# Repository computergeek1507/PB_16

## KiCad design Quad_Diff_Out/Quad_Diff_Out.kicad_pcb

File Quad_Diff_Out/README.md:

# Copyright and Disclaimer
Copyright: Scott Hanson

This documentation describes Open Hardware and is licensed under the CERN Open Hardware License Version 2 - Strongly Reciprocal. (CERN-OHL-S)

You may redistribute and modify this documentation under the terms of the CERN OHL-S-v2 (https://ohwr.org/cern_ohl_s_v2.txt). This documentation is distributed WITHOUT ANY EXPRESS OR IMPLIED WARRANTY, INCLUDING OF MERCHANTABILITY, SATISFACTORY QUALITY AND FITNESS FOR A PARTICULAR PURPOSE. Please see the CERN OHL v2-S for applicable conditions

**Under CERN OHL-S-v2, derivative work must be publicly released as defined in subsection 3.3**

# Quad Diff Out

The Quad Diff Out is a single Differental Reciever output board for the PB16. It works with Smart and Dumb Differental Recievers. All the design files are open source and available on github.

## [Part BOM](https://github.com/computergeek1507/PB_16/raw/master/Quad_Diff_Out/Quad_Diff_Out_BOM.ods)

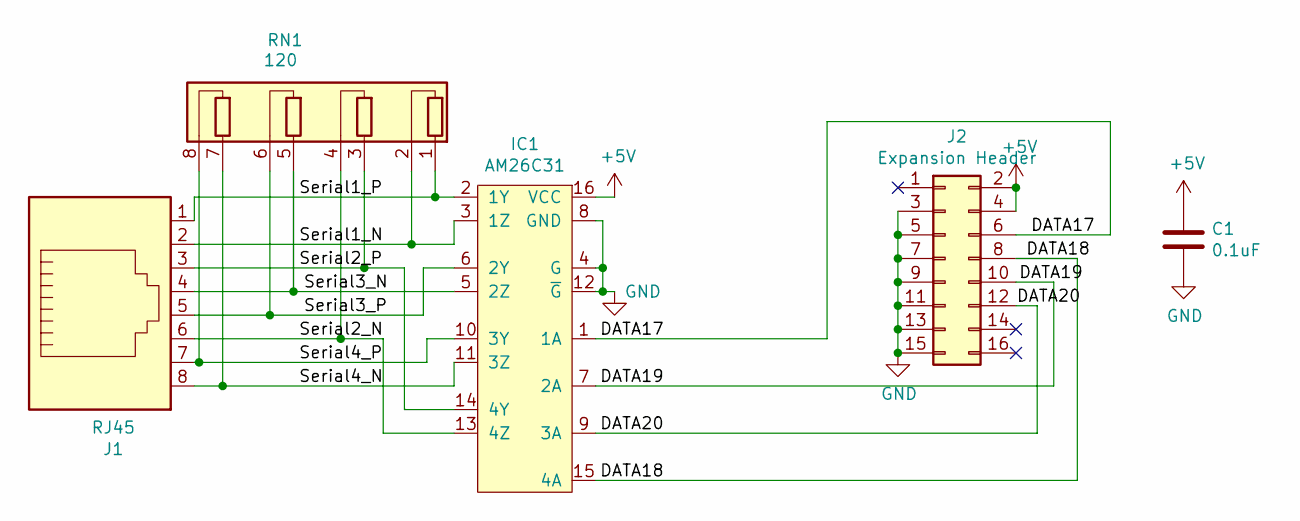
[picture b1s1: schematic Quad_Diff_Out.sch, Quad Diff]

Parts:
C1: 0.1uF; C_Rect_L7.0mm_W2.0mm_P5.00mm; Digikey PN 478-7336-1-ND
IC1: AM26C31; DIP-16_W7.62mm; Farnell 4975637
J1: RJ45; RJ45_Amphenol_54602-x08_Horizontal; Digikey PN AE10392-ND
J2: Expansion Header; PinSocket_2x08_P2.54mm_Vertical; Digikey PN S7111-ND
RN1: 120; R_Array_SIP8; Digikey PN 4608X-2-121LF-ND

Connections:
+5V: C1.1, IC1.16 (VCC), J2.2, J2.4
/DATA17: IC1.1 (1A), J2.6
/DATA18: IC1.15 (4A), J2.8
/DATA19: IC1.7 (2A), J2.10
/DATA20: IC1.9 (3A), J2.12
/Serial1_N: IC1.3 (1Z), J1.2, RN1.2 (R1.2)
/Serial1_P: IC1.2 (1Y), J1.1, RN1.1 (R1.1)
/Serial2_N: IC1.13 (4Z), J1.6, RN1.4 (R2.2)
/Serial2_P: IC1.14 (4Y), J1.3, RN1.3 (R2.1)
/Serial3_N: IC1.5 (2Z), J1.4, RN1.5 (R3.1)
/Serial3_P: IC1.6 (2Y), J1.5, RN1.6 (R3.2)
/Serial4_N: IC1.11 (3Z), J1.8, RN1.7 (R4.1)
/Serial4_P: IC1.10 (3Y), J1.7, RN1.8 (R4.2)
GND: C1.2, IC1.4 (G), IC1.8 (GND), IC1.12 (~G), J2.3, J2.5, J2.7, J2.9, J2.11, J2.13, J2.15

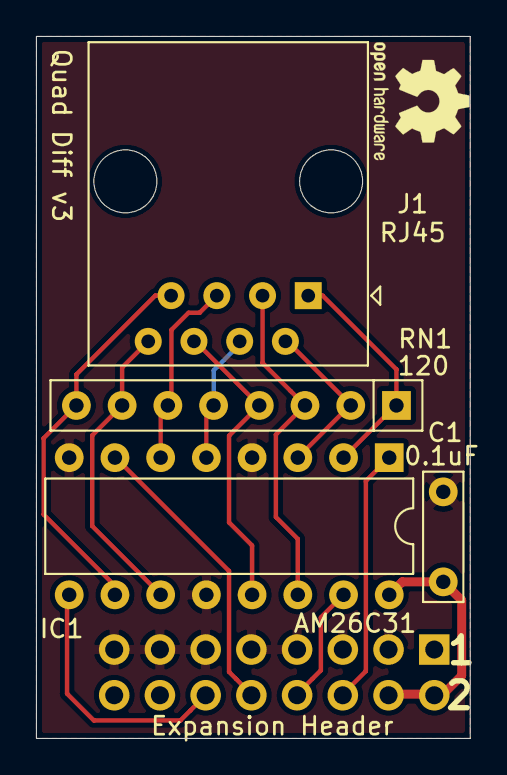
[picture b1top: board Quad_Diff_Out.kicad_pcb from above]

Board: 2 copper layers, 24.1 x 39.0 mm, 5 parts (1 on the bottom side), 14 nets.

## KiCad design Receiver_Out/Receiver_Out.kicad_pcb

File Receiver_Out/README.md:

# Copyright and Disclaimer
Copyright: Scott Hanson

This documentation describes Open Hardware and is licensed under the CERN Open Hardware License Version 2 - Strongly Reciprocal. (CERN-OHL-S)

You may redistribute and modify this documentation under the terms of the CERN OHL-S-v2 (https://ohwr.org/cern_ohl_s_v2.txt). This documentation is distributed WITHOUT ANY EXPRESS OR IMPLIED WARRANTY, INCLUDING OF MERCHANTABILITY, SATISFACTORY QUALITY AND FITNESS FOR A PARTICULAR PURPOSE. Please see the CERN OHL v2-S for applicable conditions

**Under CERN OHL-S-v2, derivative work must be publicly released as defined in subsection 3.3**

# Receiver Out

The "Receiver Out" is a 4 port Differental Reciver output board for the PB16.  All the design files are open source and available on github.

## [Part BOM](https://github.com/computergeek1507/PB_16/raw/master/Receiver_Out/Receiver_Out_BOM.ods)

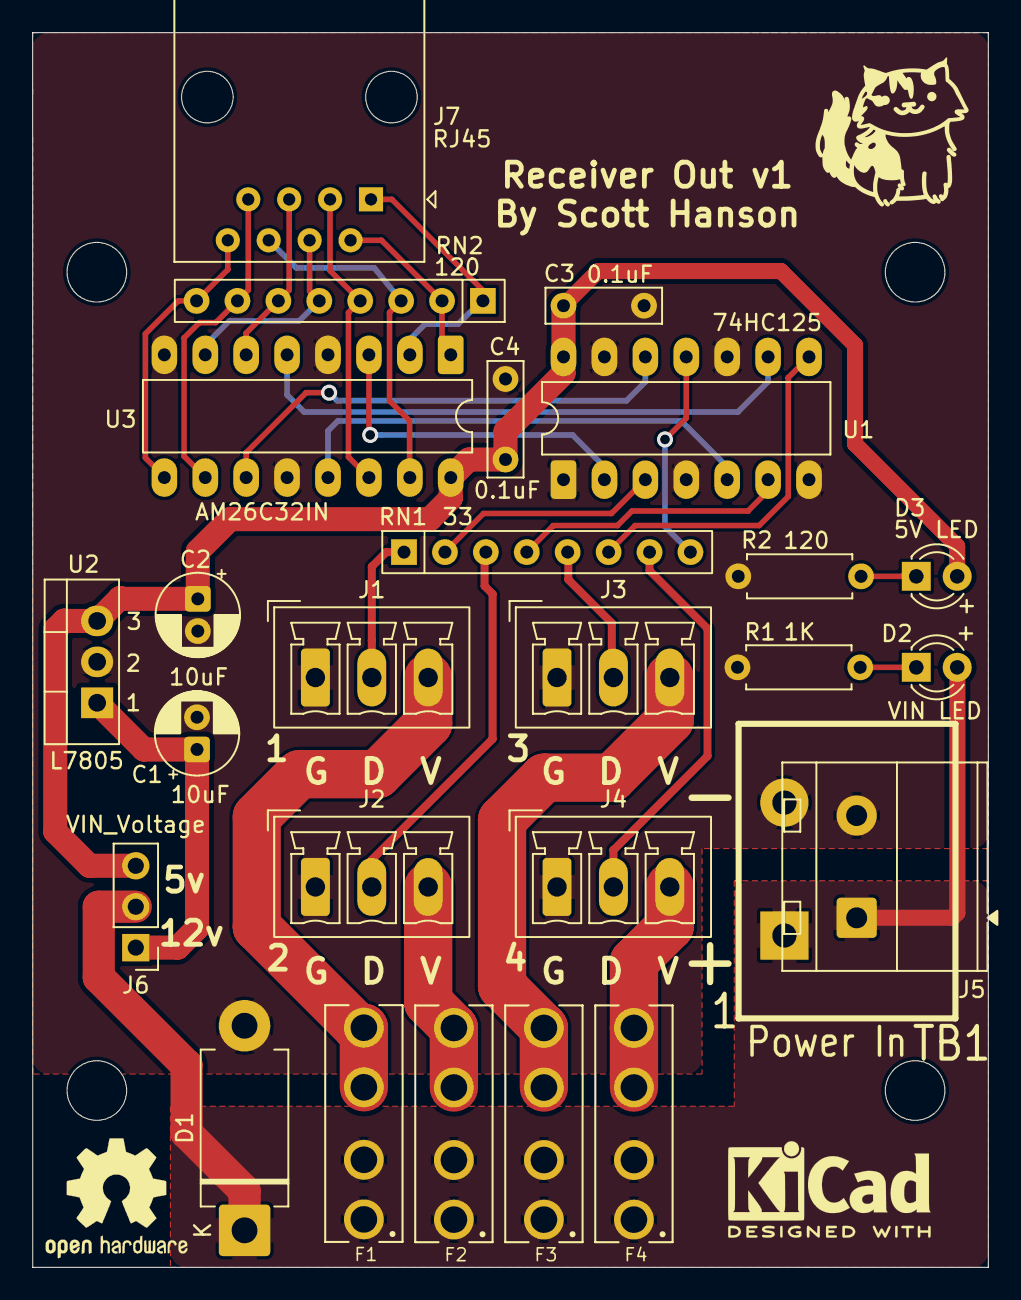
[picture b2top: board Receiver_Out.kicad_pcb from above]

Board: 2 copper layers, 59.3 x 76.7 mm, 26 parts (0 on the bottom side), 30 nets.

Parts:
C1, C2: 10uF; CP_Radial_D5.0mm_P2.00mm
C3, C4: 0.1uF; C_Rect_L7.0mm_W2.0mm_P5.00mm
D1: SB5100-T; D_DO-201AD_P12.70mm_Horizontal
D2: VIN LED; LED_D3.0mm_Clear
D3: 5V LED; LED_D3.0mm_Clear
F1, F2, F3, F4: 3544-2; FUSE_3544-2
J1: String1; PhoenixContact_MCV_1,5_3-G-3.5_1x03_P3.50mm_Vertical
J2: String2; PhoenixContact_MCV_1,5_3-G-3.5_1x03_P3.50mm_Vertical
J3: String3; PhoenixContact_MCV_1,5_3-G-3.5_1x03_P3.50mm_Vertical
J4: String4; PhoenixContact_MCV_1,5_3-G-3.5_1x03_P3.50mm_Vertical
J5: Power In; TerminalBlock_MetzConnect_Type701_RT11L02HGLU_1x02_P6.35mm_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
J6: VIN_Voltage; PinHeader_1x03_P2.54mm_Vertical
J7: RJ45; RJ45_Amphenol_54602-x08_Horizontal
R1: 1K; R_Axial_DIN0207_L6.3mm_D2.5mm_P7.62mm_Horizontal
R2: 120; R_Axial_DIN0207_L6.3mm_D2.5mm_P7.62mm_Horizontal
RN1: 33; R_Array_SIP8
RN2: 120; R_Array_SIP8
TB1: Power In; BARRIER_BLOCK_1ROW_2POS
U1: 74HC125; DIP-14_W7.62mm_LongPads
U2: L7805; TO-220-3_Vertical
U3: AM26C32IN; DIP-16_W7.62mm_LongPads

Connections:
+5V: C2.1, C3.1, C4.1, D3.2, J6.3, U1.14, U2.3, U3.16
/Diff In/Serial1_N: J7.2, RN2.2, U3.1
/Diff In/Serial1_P: J7.1, RN2.1, U3.2
/Diff In/Serial2_N: J7.6, RN2.3, U3.15
/Diff In/Serial2_P: J7.3, RN2.4, U3.14
/Diff In/Serial3_N: J7.4, RN2.5, U3.7
/Diff In/Serial3_P: J7.5, RN2.6, U3.6
/Diff In/Serial4_N: J7.8, RN2.8, U3.9
/Diff In/Serial4_P: J7.7, RN2.7, U3.10
/Outputs/DOUT1: J1.2, RN1.1
/Outputs/DOUT2: J2.2, RN1.3
/Outputs/DOUT3: J3.2, RN1.5
/Outputs/DOUT4: J4.2, RN1.7
/Outputs/VOUT1: F1.2_1, F1.2_2, J1.3
/Outputs/VOUT2: F2.2_1, F2.2_2, J2.3
/Outputs/VOUT3: F3.2_1, F3.2_2, J3.3
/Outputs/VOUT4: F4.2_1, F4.2_2, J4.3
/PWR: C1.1, J6.1, U2.1
GND: C1.2, C2.2, C3.2, C4.2, D1.2, J1.1, J2.1, J3.1, J4.1, J5.2, R1.1, R2.1, TB1.2, U1.1, U1.4, U1.7, U1.10, U1.13, U2.2, U3.4, U3.8, U3.12
unnamed: D2.1, R1.2
unnamed: D3.1, R2.2
unnamed: RN1.2, U1.3
unnamed: RN1.4, U1.6
unnamed: RN1.6, U1.8
unnamed: RN1.8, U1.11
OUT17: U1.2, U3.3
OUT18: U1.5, U3.13
OUT19: U1.9, U3.5
OUT20: U1.12, U3.11
VIN1: D1.1, D2.2, F1.1_1, F1.1_2, F2.1_1, F2.1_2, F3.1_1, F3.1_2, F4.1_1, F4.1_2, J5.1, J6.2, TB1.1

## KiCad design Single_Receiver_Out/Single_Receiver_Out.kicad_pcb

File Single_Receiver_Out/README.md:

# Copyright and Disclaimer
Copyright: Scott Hanson

This documentation describes Open Hardware and is licensed under the CERN Open Hardware License Version 2 - Strongly Reciprocal. (CERN-OHL-S)

You may redistribute and modify this documentation under the terms of the CERN OHL-S-v2 (https://ohwr.org/cern_ohl_s_v2.txt). This documentation is distributed WITHOUT ANY EXPRESS OR IMPLIED WARRANTY, INCLUDING OF MERCHANTABILITY, SATISFACTORY QUALITY AND FITNESS FOR A PARTICULAR PURPOSE. Please see the CERN OHL v2-S for applicable conditions

**Under CERN OHL-S-v2, derivative work must be publicly released as defined in subsection 3.3**

# Single Receiver Out

The "Single Receiver Out" is a 1 port Differental Reciver output board for the "Pwr Diff Expansion". Power is also provided over two of the Cat5 wires. All the design files are open source and available on github.

## [Part BOM](https://github.com/computergeek1507/PB_16/raw/master/Single_Receiver_Out/Single_Receiver_Out_BOM.ods)

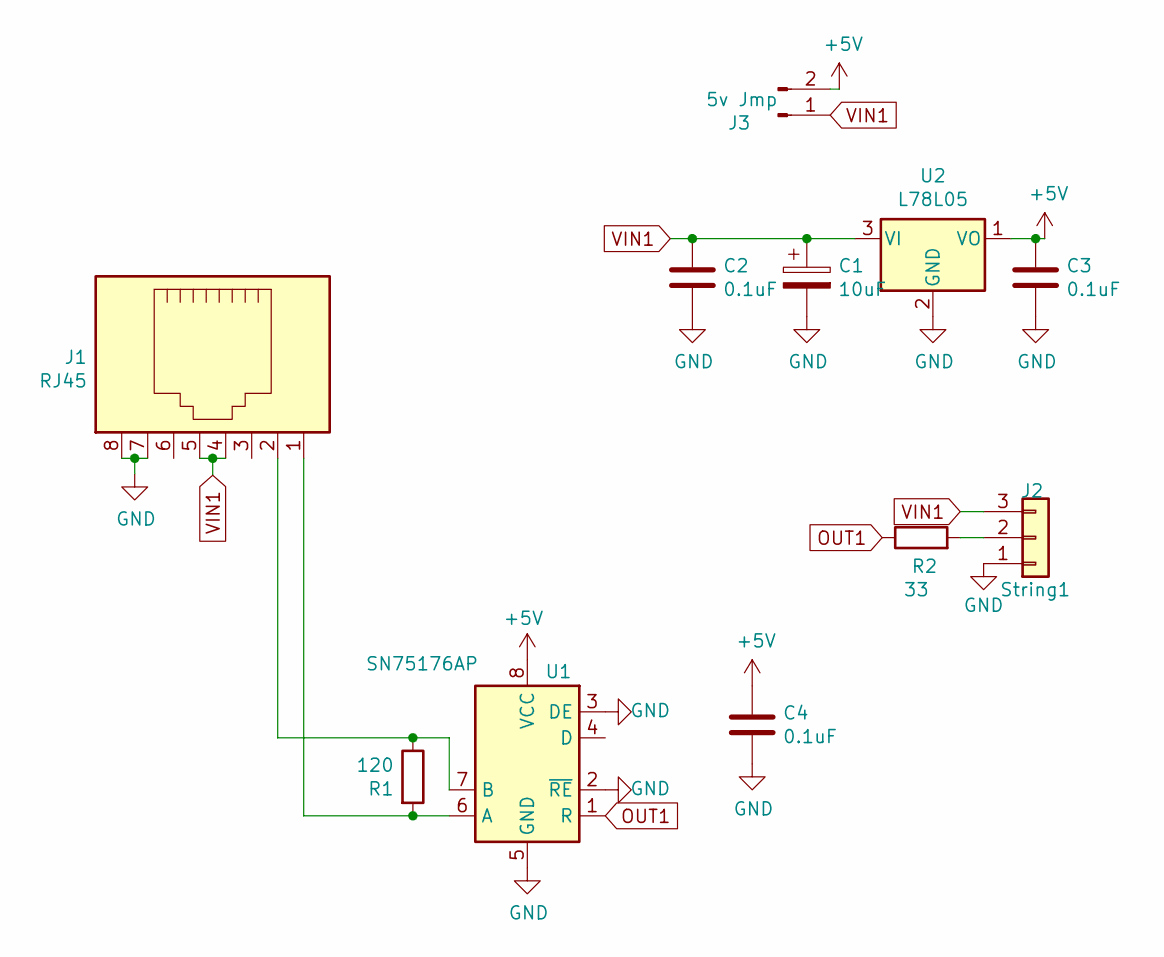
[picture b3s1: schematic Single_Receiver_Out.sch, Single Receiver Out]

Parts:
C1: 10uF; C_Rect_L7.0mm_W2.0mm_P5.00mm; MPN FK26X7R1E106K; Digi-Key_PN 445-FK26X7R1E106K-ND
C2, C3, C4: 0.1uF; C_Rect_L7.0mm_W2.0mm_P5.00mm; MPN SR215C104KARTR1; Digi-Key_PN 478-7336-1-ND
J1: RJ45; RJ45_Amphenol_54602-x08_Horizontal; MPN A-2014-2-4-R; Digi-Key_PN AE10392-ND
J2: String1; PhoenixContact_MCV_1,5_3-G-3.5_1x03_P3.50mm_Vertical; MPN 1843619/OSTTJ0311530; Digi-Key_PN 277-5737-ND/ED10555-ND
J3: 5v Jmp; PinHeader_1x02_P2.54mm_Vertical; MPN 61300211121; Digi-Key_PN 732-5315-ND
R1: 120; R_Axial_DIN0207_L6.3mm_D2.5mm_P7.62mm_Horizontal; MPN CF14JT120R; Digi-Key_PN CF14JT120RCT-ND
R2: 33; R_Axial_DIN0207_L6.3mm_D2.5mm_P7.62mm_Horizontal; MPN CF14JT33R0; Digi-Key_PN CF14JT33R0CT-ND
U1: SN75176AP; DIP-8_W7.62mm; MPN SN75176AP; Digi-Key_PN 296-1737-5-ND
U2: L78L05; TO-92_Inline; MPN MC78L05BP-AP; Digi-Key_PN MC78L05BP-APMSCT-ND

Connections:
+5V: C3.1, C4.1, J3.2, U1.8 (VCC), U2.1 (VO)
GND: C1.2, C2.2, C3.2, C4.2, J1.7, J1.8, J2.1, U1.2 (~RE), U1.3 (DE), U1.5 (GND), U2.2 (GND)
unnamed: J1.1, R1.2, U1.6 (A)
unnamed: J1.2, R1.1, U1.7 (B)
unnamed: J2.2, R2.2
OUT1: R2.1, U1.1 (R)
VIN1: C1.1, C2.1, J1.4, J1.5, J2.3, J3.1, U2.3 (VI)

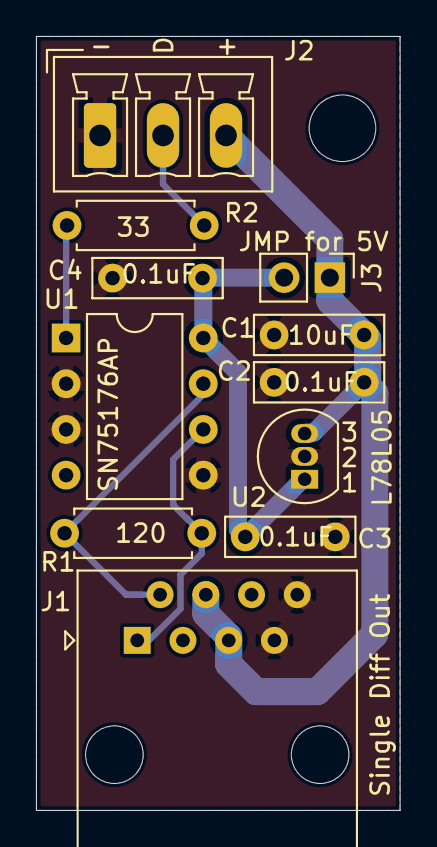
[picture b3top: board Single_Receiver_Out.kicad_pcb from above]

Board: 2 copper layers, 20.2 x 43.0 mm, 11 parts (0 on the bottom side), 7 nets.

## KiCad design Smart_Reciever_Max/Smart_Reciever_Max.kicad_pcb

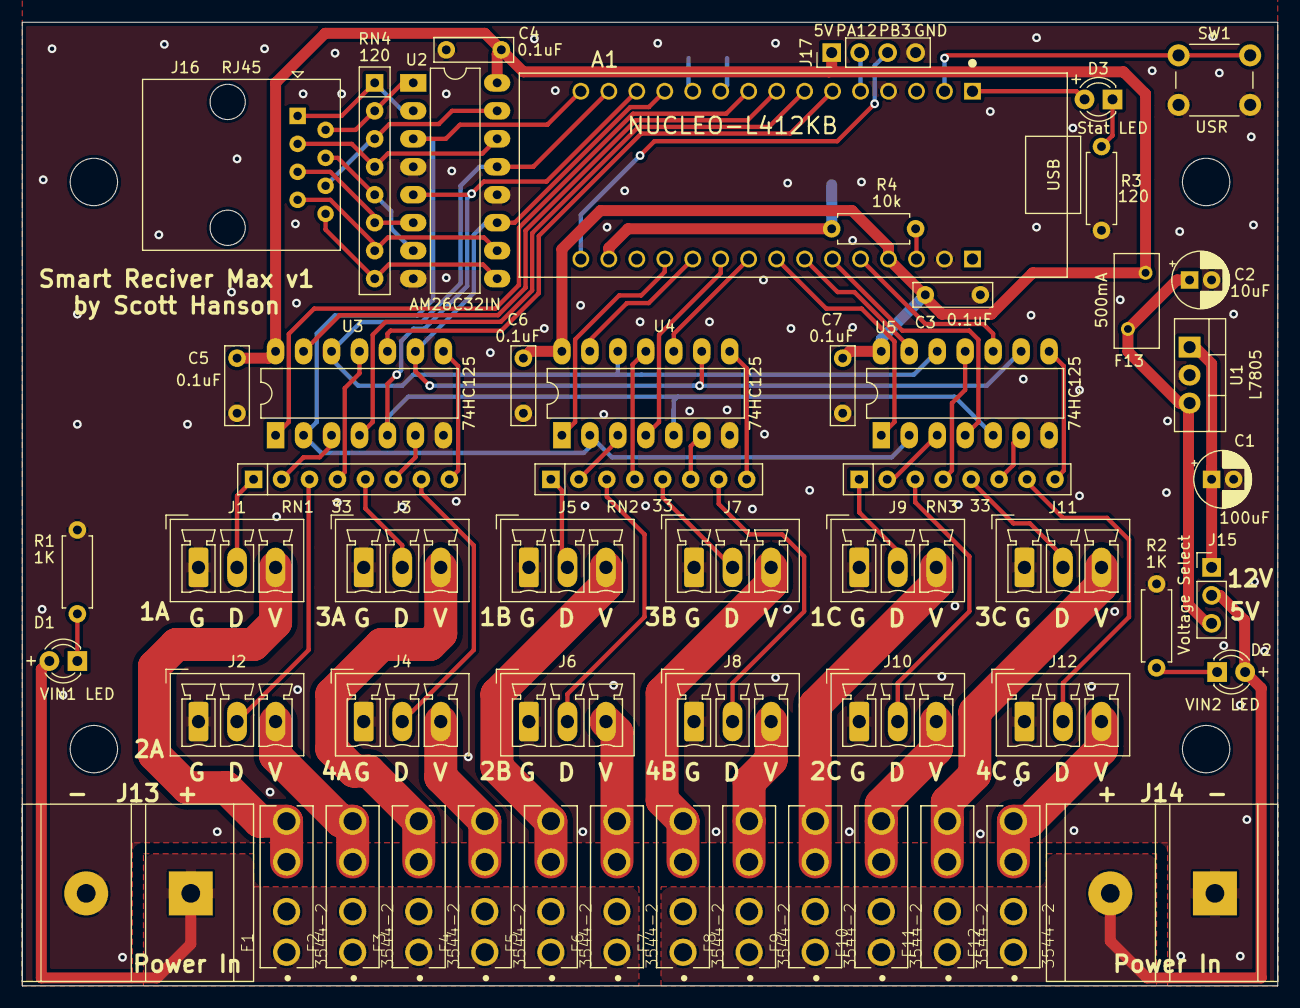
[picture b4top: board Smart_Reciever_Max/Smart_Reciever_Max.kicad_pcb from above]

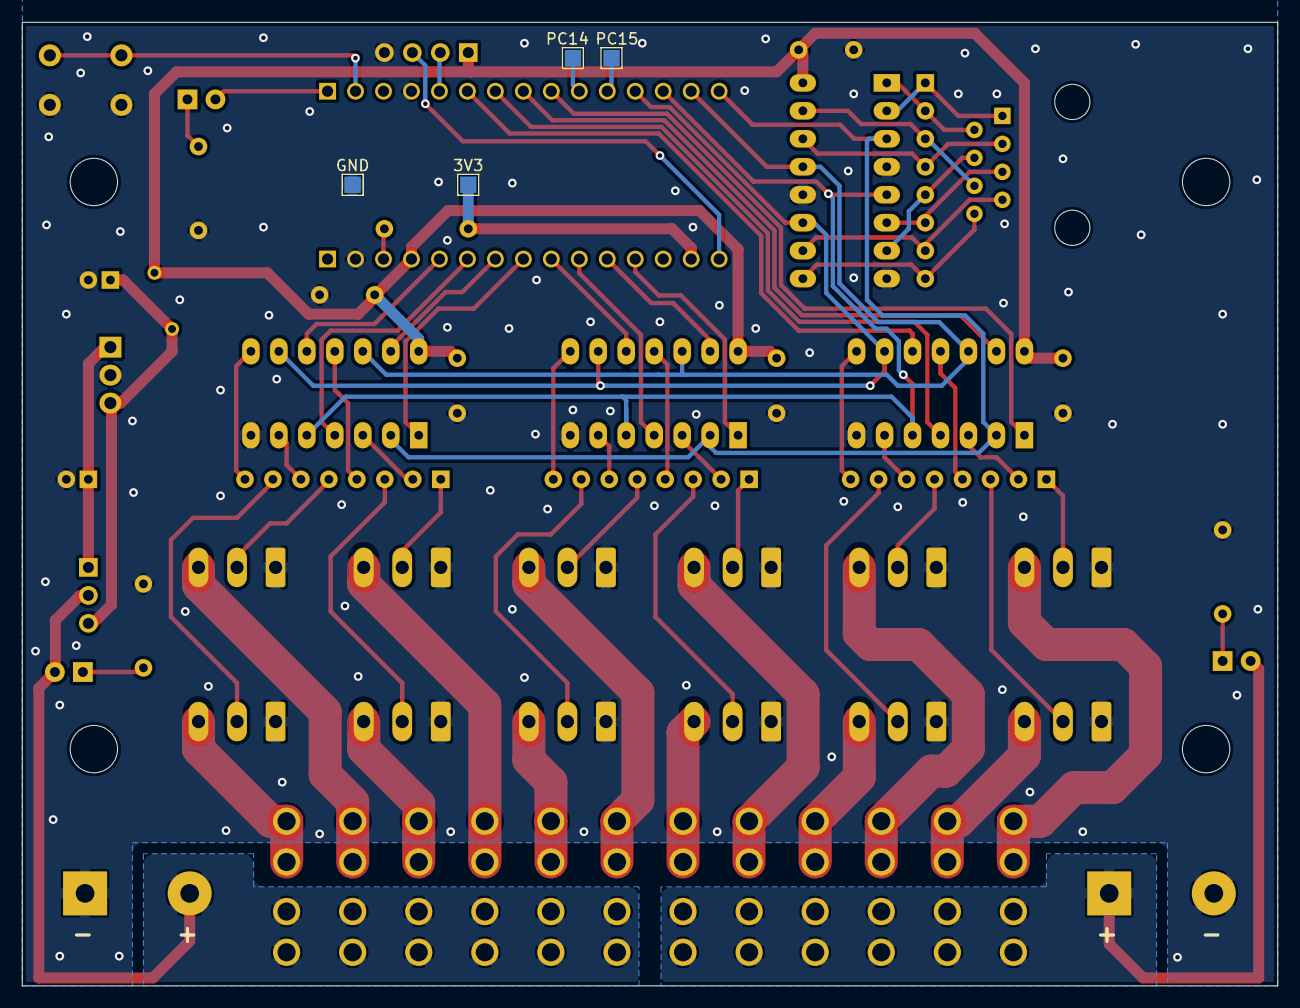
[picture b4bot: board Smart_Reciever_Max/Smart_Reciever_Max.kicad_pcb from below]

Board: 2 copper layers, 114.0 x 87.5 mm, 63 parts (4 on the bottom side), 77 nets.

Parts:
A1: NUCLEO-L412KB; MODULE_NUCLEO-L412KB
C1: 100uF; CP_Radial_D5.0mm_P2.00mm
C2: 10uF; CP_Radial_D5.0mm_P2.00mm
C3, C4, C5, C6, C7: 0.1uF; C_Rect_L7.0mm_W2.0mm_P5.00mm
D1: VIN1 LED; LED_D3.0mm_Clear
D2: VIN2 LED; LED_D3.0mm_Clear
D3: Stat LED; LED_D3.0mm_Clear
F1, F2, F3, F4, F5, F6, F7, F8, F9, F10, F11, F12: 3544-2; FUSE_3544-2
F13: 500mA; Fuse_BelFuse_0ZRE0005FF_L8.3mm_W3.8mm
H1, H2, H3, H4: MountingHole; MountingHole_4.3mm_M4
J1: String1; PhoenixContact_MCV_1,5_3-G-3.5_1x03_P3.50mm_Vertical
J2: String2; PhoenixContact_MCV_1,5_3-G-3.5_1x03_P3.50mm_Vertical
J3: String3; PhoenixContact_MCV_1,5_3-G-3.5_1x03_P3.50mm_Vertical
J4: String4; PhoenixContact_MCV_1,5_3-G-3.5_1x03_P3.50mm_Vertical
J5: String5; PhoenixContact_MCV_1,5_3-G-3.5_1x03_P3.50mm_Vertical
J6: String6; PhoenixContact_MCV_1,5_3-G-3.5_1x03_P3.50mm_Vertical
J7: String7; PhoenixContact_MCV_1,5_3-G-3.5_1x03_P3.50mm_Vertical
J8: String8; PhoenixContact_MCV_1,5_3-G-3.5_1x03_P3.50mm_Vertical
J9: String9; PhoenixContact_MCV_1,5_3-G-3.5_1x03_P3.50mm_Vertical
J10: String10; PhoenixContact_MCV_1,5_3-G-3.5_1x03_P3.50mm_Vertical
J11: String11; PhoenixContact_MCV_1,5_3-G-3.5_1x03_P3.50mm_Vertical
J12: String12; PhoenixContact_MCV_1,5_3-G-3.5_1x03_P3.50mm_Vertical
J13, J14: Power In; BARRIER_BLOCK_1ROW_2POS_P9.5MM
J15: VIN_Voltage; PinHeader_1x03_P2.54mm_Vertical
J16: RJ45; RJ45_Amphenol_54602-x08_Horizontal
J17: EXT1; PinHeader_1x04_P2.54mm_Vertical
R1, R2: 1K; R_Axial_DIN0207_L6.3mm_D2.5mm_P7.62mm_Horizontal
R3: 120; R_Axial_DIN0207_L6.3mm_D2.5mm_P7.62mm_Horizontal
R4: 10k; R_Axial_DIN0207_L6.3mm_D2.5mm_P7.62mm_Horizontal
RN1, RN2, RN3: 33; R_Array_SIP8
RN4: 120; R_Array_SIP8
SW1: USR; SW_PUSH_6mm
TP1: PC14; TestPoint_Pad_1.5x1.5mm
TP2: PC15; TestPoint_Pad_1.5x1.5mm
TP3: 3V3; TestPoint_Pad_1.5x1.5mm
TP4: GND; TestPoint_Pad_1.5x1.5mm
U1: L7805; TO-220-3_Vertical
U2: AM26C32IN; DIP-16_W7.62mm_LongPads
U3, U4, U5: 74HC125; DIP-14_W7.62mm_LongPads

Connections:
5IN: C2.1, F13.2, J15.3, U1.3
+3V3: A1.4.14, R4.1, TP3.1
+5V: A1.4.4, C3.1, C4.1, C5.1, C6.1, C7.1, F13.1, J17.1, U2.16, U3.14, U4.14, U5.14
/Outputs/DOUT1: J1.2, RN1.1
/Outputs/DOUT2: J2.2, RN1.3
/Outputs/DOUT3: J3.2, RN1.5
/Outputs/DOUT4: J4.2, RN1.7
/Outputs/DOUT5: J5.2, RN2.1
/Outputs/DOUT6: J6.2, RN2.3
/Outputs/DOUT7: J7.2, RN2.5
/Outputs/DOUT8: J8.2, RN2.7
/Outputs/DOUT9: J9.2, RN3.1
/Outputs/DOUT10: J10.2, RN3.3
/Outputs/DOUT11: J11.2, RN3.5
/Outputs/DOUT12: J12.2, RN3.7
/Outputs/VOUT1: F1.2_1, F1.2_2, J1.3
/Outputs/VOUT2: F2.2_1, F2.2_2, J2.3
/Outputs/VOUT3: F3.2_1, F3.2_2, J3.3
/Outputs/VOUT4: F4.2_1, F4.2_2, J4.3
/Outputs/VOUT5: F5.2_1, F5.2_2, J5.3
/Outputs/VOUT6: F6.2_1, F6.2_2, J6.3
/Outputs/VOUT7: F7.2_1, F7.2_2, J7.3
/Outputs/VOUT8: F8.2_1, F8.2_2, J8.3
/Outputs/VOUT9: F9.2_1, F9.2_2, J9.3
/Outputs/VOUT10: F10.2_1, F10.2_2, J10.3
/Outputs/VOUT11: F11.2_1, F11.2_2, J11.3
/Outputs/VOUT12: F12.2_1, F12.2_2, J12.3
/PWR: C1.1, J15.1, U1.1
/Serial/Serial1_N: J16.2, RN4.2, U2.1
/Serial/Serial1_P: J16.1, RN4.1, U2.2
/Serial/Serial2_N: J16.6, RN4.3, U2.15
/Serial/Serial2_P: J16.3, RN4.4, U2.14
/Serial/Serial3_N: J16.4, RN4.5, U2.7
/Serial/Serial3_P: J16.5, RN4.6, U2.6
/Serial/Serial4_N: J16.8, RN4.8, U2.9
/Serial/Serial4_P: J16.7, RN4.7, U2.10
DATA1: A1.3.15, U2.3, U3.2, U4.2, U5.2
DATA2: A1.3.14, U2.13, U3.12, U4.12, U5.12
DATA3: A1.3.13, U2.5, U3.5, U4.5, U5.5
DATA4: A1.3.12, U2.11, U3.9, U4.9, U5.9
EN1A: A1.3.9, U3.1
EN1B: A1.4.12, U4.1
EN1C: A1.4.8, U5.1
EN2A: A1.3.8, U3.13
EN2B: A1.4.11, U4.13
EN2C: A1.4.7, U5.13
EN3A: A1.3.7, U3.4
EN3B: A1.4.10, U4.4
EN3C: A1.4.6, U5.4
EN4A: A1.3.6, U3.10
EN4B: A1.4.9, U4.10
EN4C: A1.4.5, U5.10
GND: A1.3.4, A1.4.2, C1.2, C2.2, C3.2, C4.2, C5.2, C6.2, C7.2, J1.1, J2.1, J3.1, J4.1, J5.1, J6.1, J7.1, J8.1, J9.1, J10.1, J11.1, J12.1, J13.2, J14.1, J17.4, R1.1, R2.1, R3.1, SW1.2, TP4.1, U1.2, U2.4, U2.8, U2.12, U3.7, U4.7, U5.7
unnamed: A1.3.1, D3.2
unnamed: A1.4.3, R4.2
unnamed: D1.1, R1.2
unnamed: D2.1, R2.2
unnamed: D3.1, R3.2
unnamed: RN1.2, U3.3
unnamed: RN1.4, U3.11
unnamed: RN1.6, U3.6
unnamed: RN1.8, U3.8
unnamed: RN2.2, U4.3
unnamed: RN2.4, U4.11
unnamed: RN2.6, U4.6
unnamed: RN2.8, U4.8
unnamed: RN3.2, U5.3
unnamed: RN3.4, U5.11
unnamed: RN3.6, U5.6
unnamed: RN3.8, U5.8
PA10: A1.3.2, SW1.1
PA12: A1.3.5, J17.2
PB3: A1.4.15, J17.3
PC14: A1.3.10, TP1.1
PC15: A1.3.11, TP2.1
VIN1: D1.2, F1.1_1, F1.1_2, F2.1_1, F2.1_2, F3.1_1, F3.1_2, F4.1_1, F4.1_2, F5.1_1, F5.1_2, F6.1_1, F6.1_2, J13.1
VIN2: D2.2, F7.1_1, F7.1_2, F8.1_1, F8.1_2, F9.1_1, F9.1_2, F10.1_1, F10.1_2, F11.1_1, F11.1_2, F12.1_1, F12.1_2, J14.2, J15.2

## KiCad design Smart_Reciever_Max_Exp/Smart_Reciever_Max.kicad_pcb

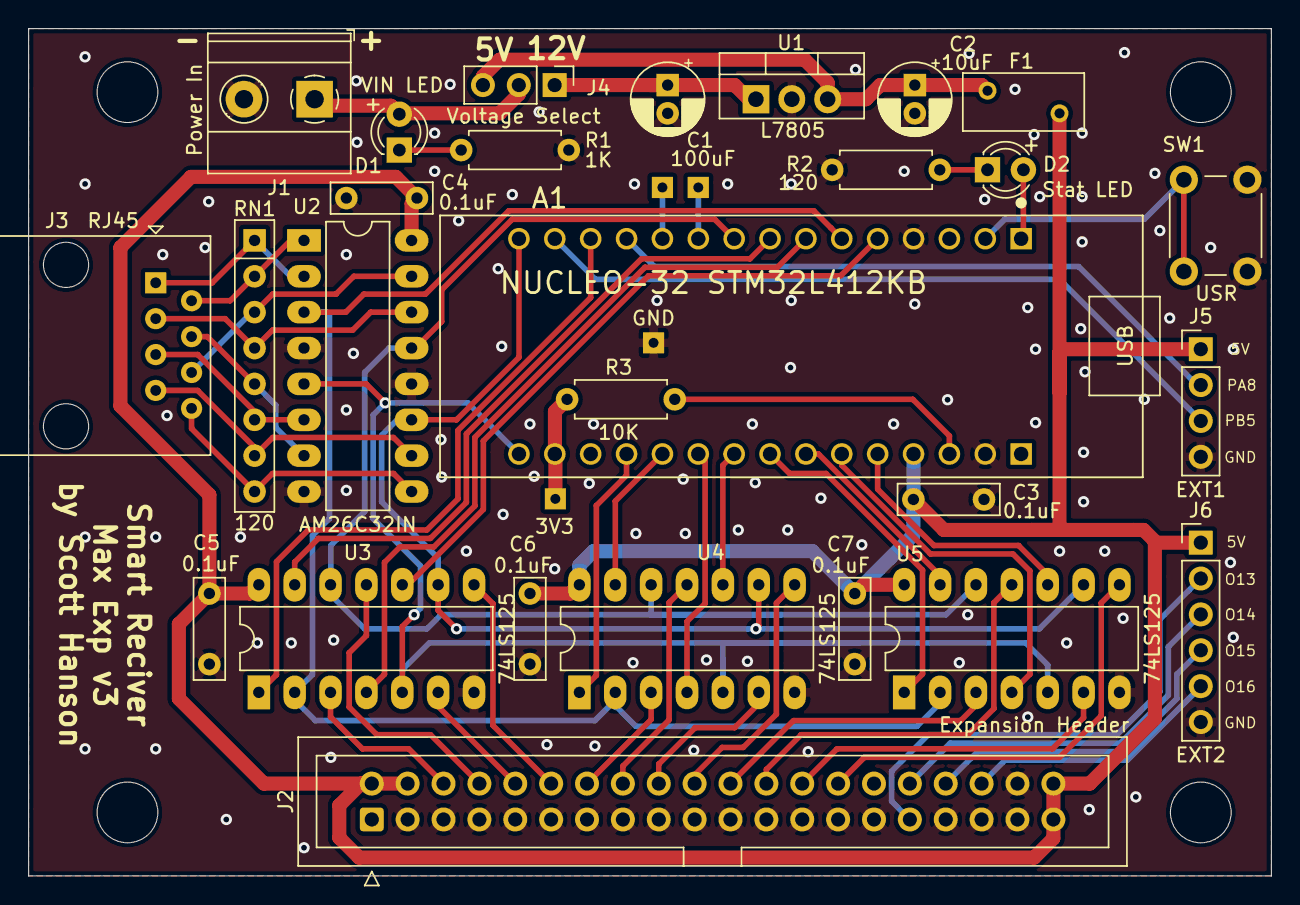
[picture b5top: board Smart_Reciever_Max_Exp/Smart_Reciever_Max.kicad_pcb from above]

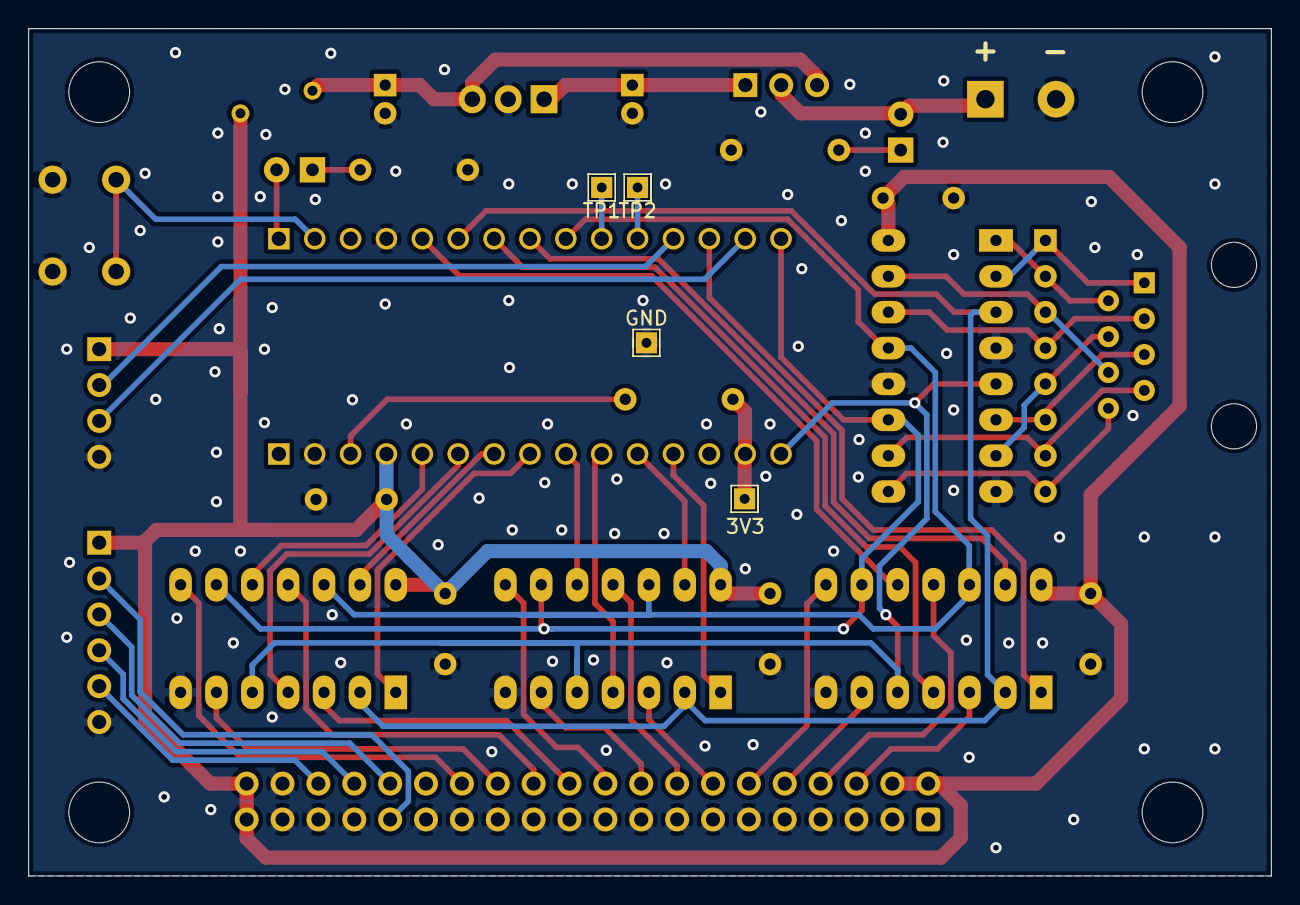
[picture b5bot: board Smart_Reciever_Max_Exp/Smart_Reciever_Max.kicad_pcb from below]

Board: 2 copper layers, 88.0 x 60.0 mm, 35 parts (4 on the bottom side), 55 nets.

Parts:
A1: NUCLEO-32 STM32L412KB; MODULE_NUCLEO-L412KB
C1: 100uF; CP_Radial_D5.0mm_P2.00mm
C2: 10uF; CP_Radial_D5.0mm_P2.00mm
C3, C4, C5, C6, C7: 0.1uF; C_Rect_L7.0mm_W2.0mm_P5.00mm
D1: VIN LED; LED_D3.0mm_Clear
D2: Stat LED; LED_D3.0mm_Clear
F1: Fuse; Fuse_BelFuse_0ZRE0005FF_L8.3mm_W3.8mm
H1, H2, H3, H4: MountingHole; MountingHole_4.3mm_M4
J1: Power In; TerminalBlock_Phoenix_MKDS-1,5-2_1x02_P5.00mm_Horizontal
J2: Expansion Header; IDC-Header_2x20_P2.54mm_Vertical
J3: RJ45; RJ45_Amphenol_54602-x08_Horizontal
J4: VIN_Voltage; PinHeader_1x03_P2.54mm_Vertical
J5: EXT1; PinHeader_1x04_P2.54mm_Vertical
J6: EXT2; PinHeader_1x06_P2.54mm_Vertical
R1: 1K; R_Axial_DIN0207_L6.3mm_D2.5mm_P7.62mm_Horizontal
R2: 120; R_Axial_DIN0207_L6.3mm_D2.5mm_P7.62mm_Horizontal
R3: 10K; R_Axial_DIN0207_L6.3mm_D2.5mm_P7.62mm_Horizontal
RN1: 120; R_Array_SIP8
SW1: USR; SW_PUSH_6mm
TP1: PC14; TestPoint_THTPad_1.5x1.5mm_Drill0.7mm
TP2: PC15; TestPoint_THTPad_1.5x1.5mm_Drill0.7mm
TP3: 3V3; TestPoint_THTPad_1.5x1.5mm_Drill0.7mm
TP4: GND; TestPoint_THTPad_1.5x1.5mm_Drill0.7mm
U1: L7805; TO-220-3_Vertical
U2: AM26C32IN; DIP-16_W7.62mm_LongPads
U3, U4, U5: 74LS125; DIP-14_W7.62mm_LongPads

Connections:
5IN: C2.1, F1.2, J4.3, U1.3
+3V3: A1.4.14, R3.2, TP3.1
+5V: A1.4.4, C3.1, C4.1, C5.1, C6.1, C7.1, F1.1, J2.2, J2.4, J2.39, J2.40, J5.1, J6.1, U2.16, U3.14, U4.14, U5.14
/PWR: C1.1, J4.1, U1.1
/Serial/Serial1_N: J3.2, RN1.2, U2.1
/Serial/Serial1_P: J3.1, RN1.1, U2.2
/Serial/Serial2_N: J3.6, RN1.3, U2.15
/Serial/Serial2_P: J3.3, RN1.4, U2.14
/Serial/Serial3_N: J3.4, RN1.5, U2.7
/Serial/Serial3_P: J3.5, RN1.6, U2.6
/Serial/Serial4_N: J3.8, RN1.8, U2.9
/Serial/Serial4_P: J3.7, RN1.7, U2.10
DATA1: A1.3.6, U2.3, U3.2, U4.2, U5.2
DATA2: A1.3.9, U2.13, U3.12, U4.12, U5.12
DATA3: A1.4.15, U2.5, U3.5, U4.5, U5.5
DATA4: A1.3.15, U2.11, U3.9, U4.9, U5.9
EN1A: A1.3.13, U3.1
EN1B: A1.4.12, U4.1
EN1C: A1.4.8, U5.1
EN2A: A1.3.8, U3.13
EN2B: A1.4.11, U4.13
EN2C: A1.4.7, U5.13
EN3A: A1.3.7, U3.4
EN3B: A1.4.10, U4.4
EN3C: A1.4.6, U5.4
EN4A: A1.3.5, U3.10
EN4B: A1.4.9, U4.10
EN4C: A1.4.5, U5.10
GND: A1.3.4, A1.4.2, C1.2, C2.2, C3.2, C4.2, C5.2, C6.2, C7.2, J1.2, J2.3, J2.5, J2.7, J2.9, J2.11, J2.13, J2.15, J2.17, J2.19, J2.21, J2.23, J2.25, J2.27, J2.29, J2.33, J2.35, J2.37, J2.38, J5.4, J6.6, R1.1, R2.1, SW1.2, TP4.1, U1.2, U2.4, U2.8, U2.12, U3.7, U4.7, U5.7
unnamed: A1.3.1, D2.2
unnamed: A1.4.3, R3.1
unnamed: D1.1, R1.2
unnamed: D2.1, R2.2
OUT1: J2.6, U3.3
OUT2: J2.8, U3.11
OUT3: J2.10, U3.6
OUT4: J2.12, U3.8
OUT5: J2.14, U4.3
OUT6: J2.16, U4.11
OUT7: J2.18, U4.6
OUT8: J2.20, U4.8
OUT9: J2.22, U5.3
OUT10: J2.24, U5.11
OUT11: J2.26, U5.6
OUT12: J2.28, U5.8
OUT13: J2.31, J6.2
OUT14: J2.32, J6.3
OUT15: J2.34, J6.4
OUT16: J2.36, J6.5
PA8: A1.3.12, J5.2
PA10: A1.3.2, SW1.1
PB5: A1.3.14, J5.3
PC14: A1.3.10, TP1.1
PC15: A1.3.11, TP2.1
VIN2: D1.2, J1.1, J4.2

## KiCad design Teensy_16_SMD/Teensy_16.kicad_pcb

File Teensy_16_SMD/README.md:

# Copyright and Disclaimer
Copyright: Scott Hanson

This documentation describes Open Hardware and is licensed under the CERN Open Hardware Licence Version 2 - Strongly Reciprocal. (CERN-OHL-S)

You may redistribute and modify this documentation under the terms of the CERN OHL-S-v2 (https://ohwr.org/cern_ohl_s_v2.txt). This documentation is distributed WITHOUT ANY EXPRESS OR IMPLIED WARRANTY, INCLUDING OF MERCHANTABILITY, SATISFACTORY QUALITY AND FITNESS FOR A PARTICULAR PURPOSE. Please see the CERN OHL v2-S for applicable conditions

**Under CERN OHL-S-v2, derivative work must be publicy released as defined in subsection 3.3**

# Teensy 16 SMD

**WIP, Do not use**

The Teensy 16 SMD is a Teensy 4.1 based 16 port controller. All the design files are open source and available on github.

## [Interactive BOM](https://computergeek1507.github.io/PB_16/Teensy_16_SMD/bom/ibom)

## [Part BOM](https://github.com/computergeek1507/PB_16/raw/master/Teensy_16_SMD/Teensy_16_BOM.ods)

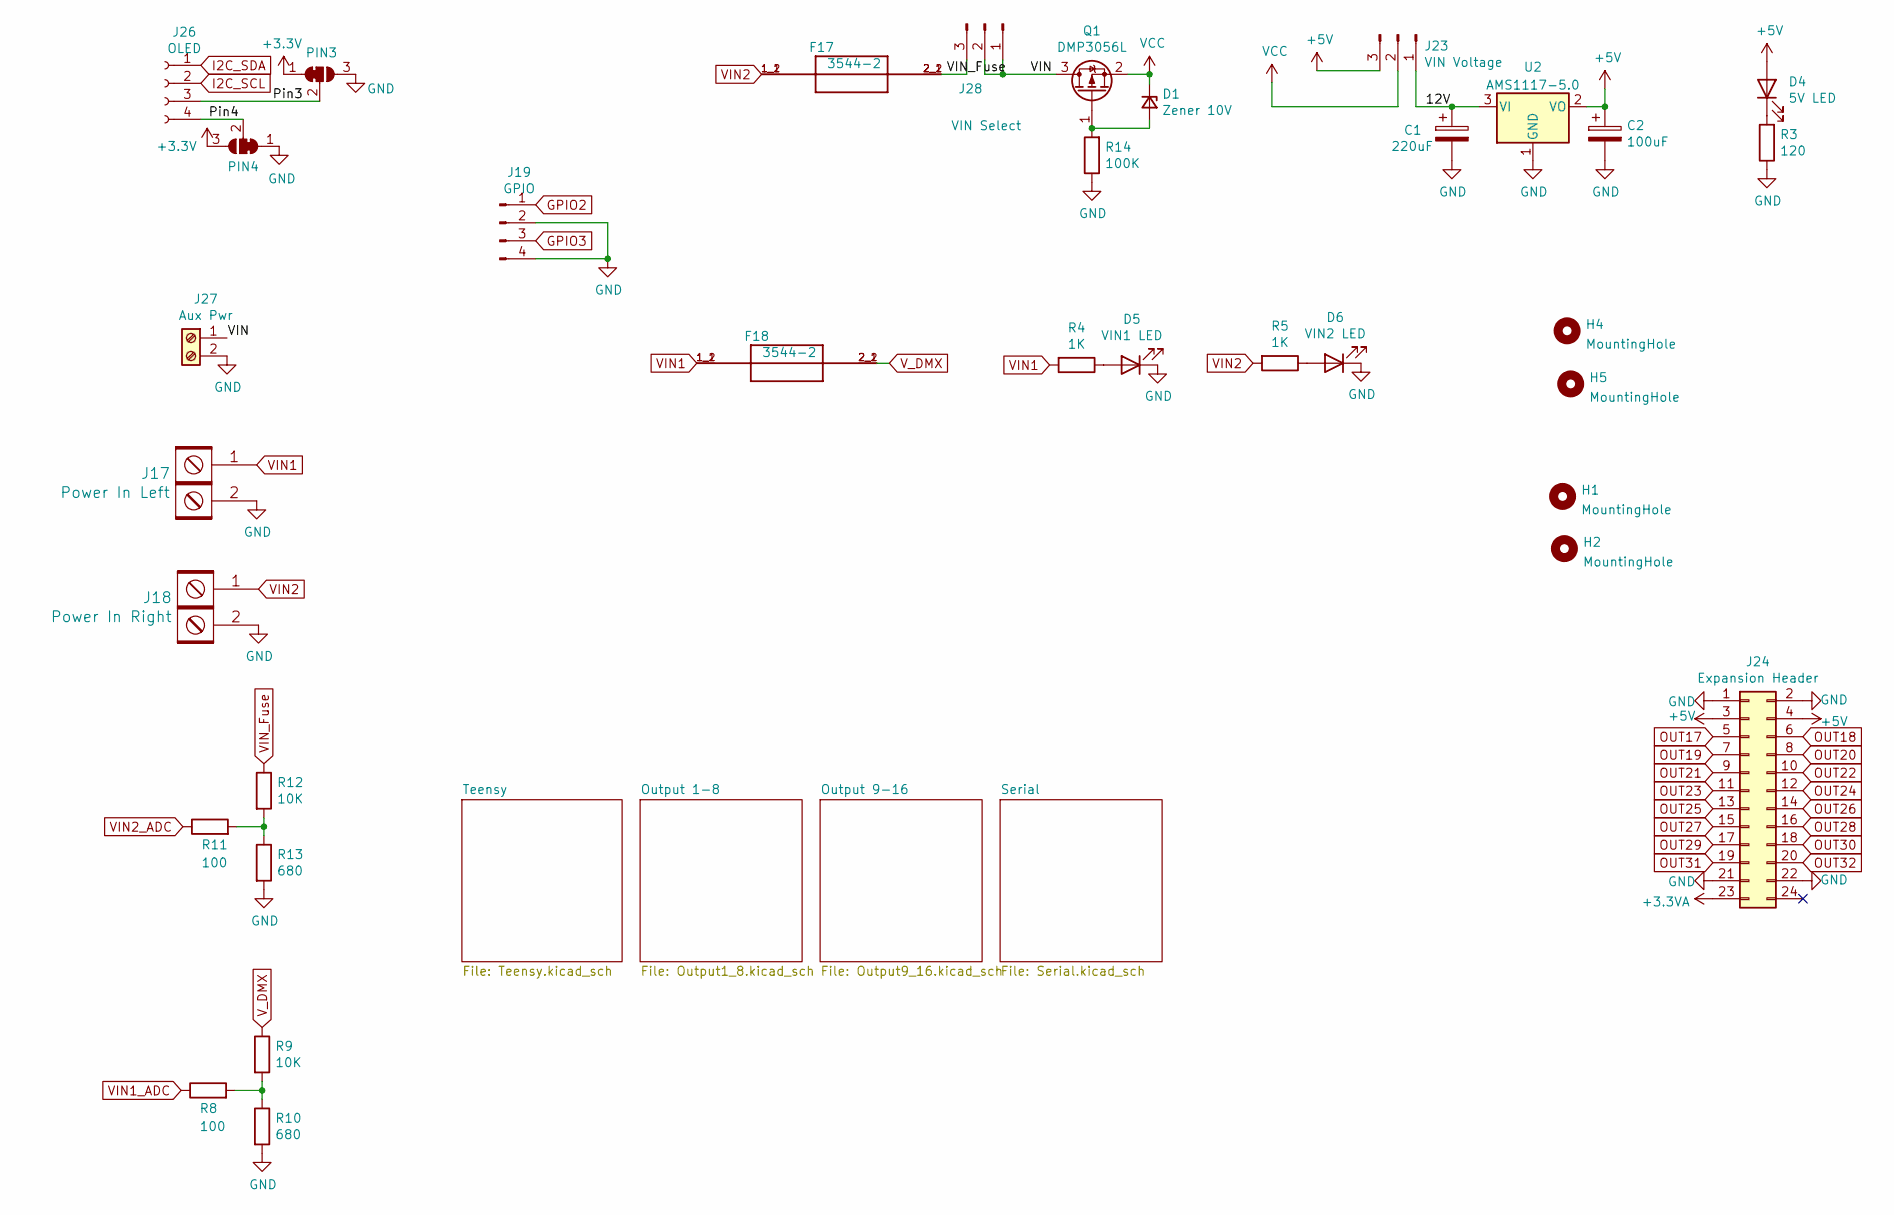
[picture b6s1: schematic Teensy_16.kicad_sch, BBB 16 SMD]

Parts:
C1: 220uF; CP_Radial_D10.0mm_P5.00mm; MPN ECA-1HM221; Digi-Key_PN P5183-ND
C2: 100uF; CP_Elec_6.3x5.4_Nichicon; MPN UWX1C101MCL1GB; Digi-Key_PN 493-2105-1-ND
D1: Zener 10V; D_SOD-123; MPN MMSZ5240B-7-F; Digi-Key_PN MMSZ5240B-FDICT-ND
D4: 5V LED; LED_0603_1608Metric_Pad1.05x0.95mm_HandSolder; MPN LTST-C190KRKT; Digi-Key_PN 160-1436-2-ND
D5: VIN1 LED; LED_0603_1608Metric_Pad1.05x0.95mm_HandSolder; MPN LTST-C190KRKT; Digi-Key_PN 160-1436-2-ND
D6: VIN2 LED; LED_0603_1608Metric_Pad1.05x0.95mm_HandSolder; MPN LTST-C190KRKT; Digi-Key_PN 160-1436-2-ND
F17, F18: 3544-2; FUSE_3544-2; MPN 3544-2; Digi-Key_PN 36-3544-2-ND
H1, H2, H4, H5: MountingHole; MountingHole_3.7mm
J17: Power In Left; BARRIER_BLOCK_1ROW_2POS_P9.5MM; MPN OSTYK51102030; Digi-Key_PN ED2953-ND
J18: Power In Right; BARRIER_BLOCK_1ROW_2POS_P9.5MM; MPN OSTYK51102030; Digi-Key_PN ED2953-ND
J19: GPIO; JST_XH_B4B-XH-A_1x04_P2.50mm_Vertical; MPN B4B-XH-A(LF)(SN); Digi-Key_PN 455-2249-ND
J23: VIN Voltage; PinHeader_1x03_P2.54mm_Vertical; MPN 61300311121; Digi-Key_PN 732-5316-ND
J24: Expansion Header; OST_302-S241; MPN 302-S241; Digi-Key_PN ED10525-ND
J26: OLED; OLED-SSD1306-128X64-I2C-THT; MPN PPTC041LFBN-RC; Digi-Key_PN S7002-ND
J27: Aux Pwr; PHOENIX_MKDS1_2-3.81; MPN 1727010; Digi-Key_PN 277-1947-ND
J28: VIN Select; PinHeader_1x03_P2.54mm_Vertical; MPN 61300311121; Digi-Key_PN 732-5316-ND
PIN3: Jumper; SolderJumper-3_P1.3mm_Bridged12_Pad1.0x1.5mm
PIN4: JUMPER; SolderJumper-3_P1.3mm_Bridged12_Pad1.0x1.5mm
Q1: DMP3056L; SOT-23; MPN DMP3056L-7; Digi-Key_PN DMP3056L-7DICT-ND
R3: 120; R_0603_1608Metric_Pad0.98x0.95mm_HandSolder; MPN CRGCQ0603F120R; Digi-Key_PN A129677CT-ND
R4, R5: 1K; R_0603_1608Metric_Pad0.98x0.95mm_HandSolder; MPN RC0603FR-071KL; Digi-Key_PN 311-1.00KHRTR-ND
R8, R11: 100; R_0603_1608Metric_Pad0.98x0.95mm_HandSolder; MPN RMCF0603FT100R; Digi-Key_PN RMCF0603FT100RCT-ND
R9, R12: 10K; R_0603_1608Metric_Pad0.98x0.95mm_HandSolder; MPN RC0603FR-0710KL; Digi-Key_PN 311-10.0KHRCT-ND
R10, R13: 680; R_0603_1608Metric_Pad0.98x0.95mm_HandSolder; MPN RC0603FR-07680RL; Digi-Key_PN 311-680HRCT-ND
R14: 100K; R_0603_1608Metric_Pad0.98x0.95mm_HandSolder; MPN RT0603BRD07100KL; Digi-Key_PN YAG1235CT-ND
U2: AMS1117-5.0; SOT-223-3_TabPin2

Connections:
+3.3VA: J24.23; also elsewhere on the board
+3V3: PIN3.1 (A), PIN4.3 (B); also elsewhere on the board
+5V: C2.1, D4.2 (A), J23.3, J24.3, J24.4, U2.2 (VO); also elsewhere on the board
/12V: C1.1, J23.1, U2.3 (VI)
/Pin3: J26.3, PIN3.2 (C)
/Pin4: J26.4, PIN4.2 (C)
/VIN: J27.1, J28.1, J28.2, Q1.3 (D)
ETH_GND: C1.2, C2.2, D5.1 (K), D6.1 (K), J17.2, J18.2, J19.2, J19.4, J24.1, J24.2, J24.21, J24.22, J27.2, PIN3.3 (B), PIN4.1 (A), R3.1, R10.2, R13.2, R14.1, U2.1 (GND); also elsewhere on the board
GPIO2: J19.1; also elsewhere on the board
GPIO3: J19.3; also elsewhere on the board
I2C_SCL: J26.2; also elsewhere on the board
I2C_SDA: J26.1; also elsewhere on the board
unnamed: D1.2 (A), Q1.1 (G), R14.2
unnamed: D4.1 (K), R3.2
unnamed: D5.2 (A), R4.1
unnamed: D6.2 (A), R5.1
unnamed: R8.2, R9.2, R10.1
unnamed: R11.2, R12.2, R13.1
OUT17: J24.5; also elsewhere on the board
OUT18: J24.6; also elsewhere on the board
OUT19: J24.7; also elsewhere on the board
OUT20: J24.8; also elsewhere on the board
OUT21: J24.9; also elsewhere on the board
OUT22: J24.10; also elsewhere on the board
OUT23: J24.11; also elsewhere on the board
OUT24: J24.12; also elsewhere on the board
OUT25: J24.13; also elsewhere on the board
OUT26: J24.14; also elsewhere on the board
OUT27: J24.15; also elsewhere on the board
OUT28: J24.16; also elsewhere on the board
OUT29: J24.17; also elsewhere on the board
OUT30: J24.18; also elsewhere on the board
OUT31: J24.19; also elsewhere on the board
OUT32: J24.20; also elsewhere on the board
VCC: D1.1 (K), J23.2, Q1.2 (S)
VIN1: F18.1_1 (1), F18.1_2 (1), J17.1, R4.2; also elsewhere on the board
VIN1_ADC: R8.1; also elsewhere on the board
VIN2: F17.1_1 (1), F17.1_2 (1), J18.1, R5.2; also elsewhere on the board
VIN2_ADC: R11.1; also elsewhere on the board
VIN_Fuse: F17.2_1 (2), F17.2_2 (2), J28.3, R12.1
V_DMX: F18.2_1 (2), F18.2_2 (2), R9.1; also elsewhere on the board

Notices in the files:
parts and their libraries:
Copyright 2016 Accelerated Designs. All rights reserved.
